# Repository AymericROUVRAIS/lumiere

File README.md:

# Lumiere

Software to control custom connected lamp.

## Objectives

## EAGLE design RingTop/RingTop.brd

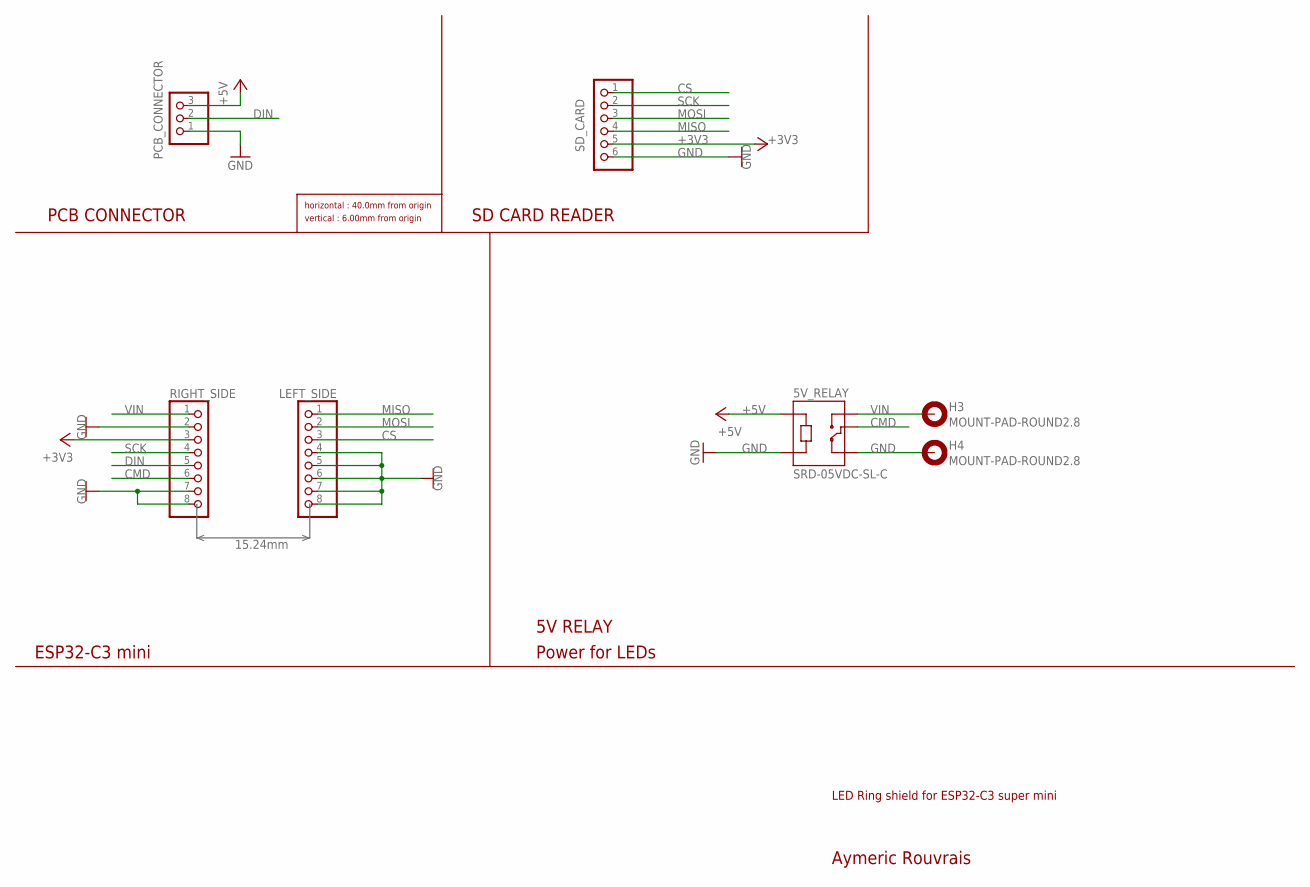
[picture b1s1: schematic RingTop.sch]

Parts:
5V_RELAY: SRD-05VDC-SL-C; RELAY_SRD-05VDC-SL-C
H3, H4: MOUNT-PAD-ROUND2.8; 2,8-PAD
LEFT_SIDE: PINHD-1X8; 1X08
PCB_CONNECTOR: PINHD-1X3; 1X03
RIGHT_SIDE: PINHD-1X8; 1X08
SD_CARD: PINHD-1X6/90; 1X06/90

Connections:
+3V3: RIGHT_SIDE.3, SD_CARD.5
+5V: 5V_RELAY.A1, PCB_CONNECTOR.3
CMD: 5V_RELAY.COM, RIGHT_SIDE.6
CS: LEFT_SIDE.3, SD_CARD.1
DIN: PCB_CONNECTOR.2, RIGHT_SIDE.5
GND: 5V_RELAY.A2, 5V_RELAY.NC, H4.B2,8, LEFT_SIDE.4, LEFT_SIDE.5, LEFT_SIDE.6, LEFT_SIDE.7, LEFT_SIDE.8, PCB_CONNECTOR.1, RIGHT_SIDE.2, RIGHT_SIDE.7, RIGHT_SIDE.8, SD_CARD.6
MISO: LEFT_SIDE.1, SD_CARD.4
MOSI: LEFT_SIDE.2, SD_CARD.3
SCK: RIGHT_SIDE.4, SD_CARD.2
VIN: 5V_RELAY.NO, H3.B2,8, RIGHT_SIDE.1

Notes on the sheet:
LED Ring shield for ESP32-C3 super mini
Aymeric Rouvrais
15.24mm
ESP32-C3 mini
PCB CONNECTOR
SD CARD READER
5V RELAY
Power for LEDs
horizontal : 40.0mm from origin
vertical : 6.00mm from origin

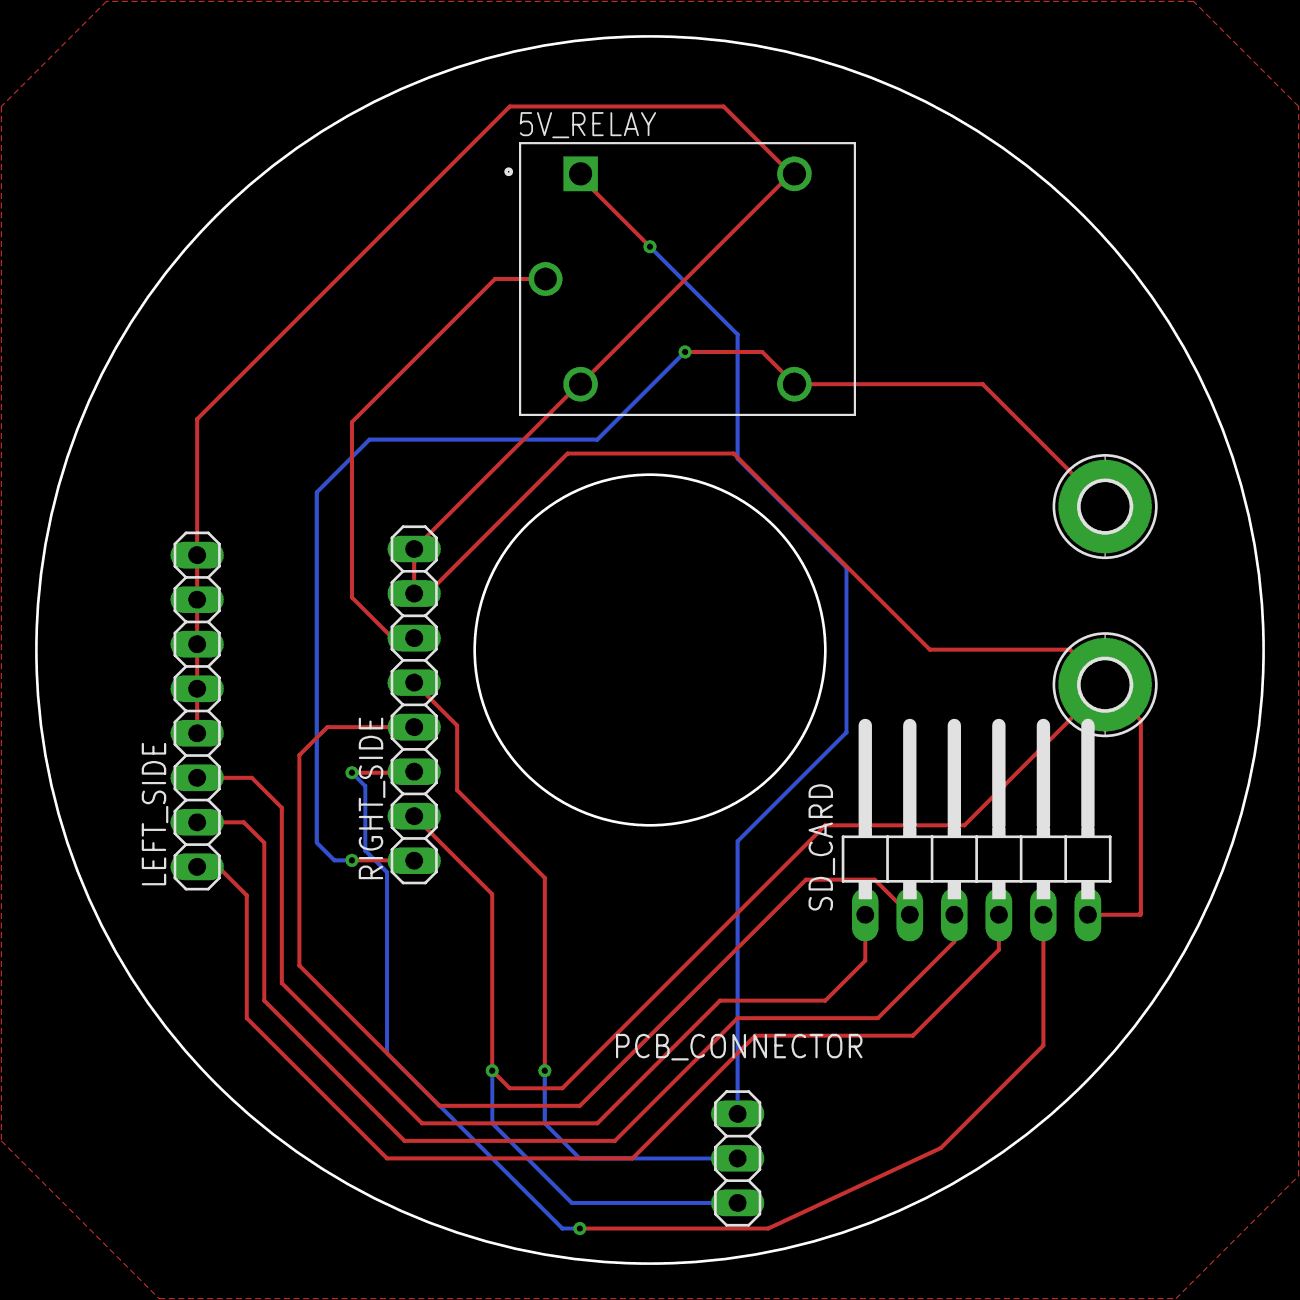
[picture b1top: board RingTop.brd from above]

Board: 2 copper layers, 70.0 x 70.0 mm, 7 parts (0 on the bottom side), 10 nets.

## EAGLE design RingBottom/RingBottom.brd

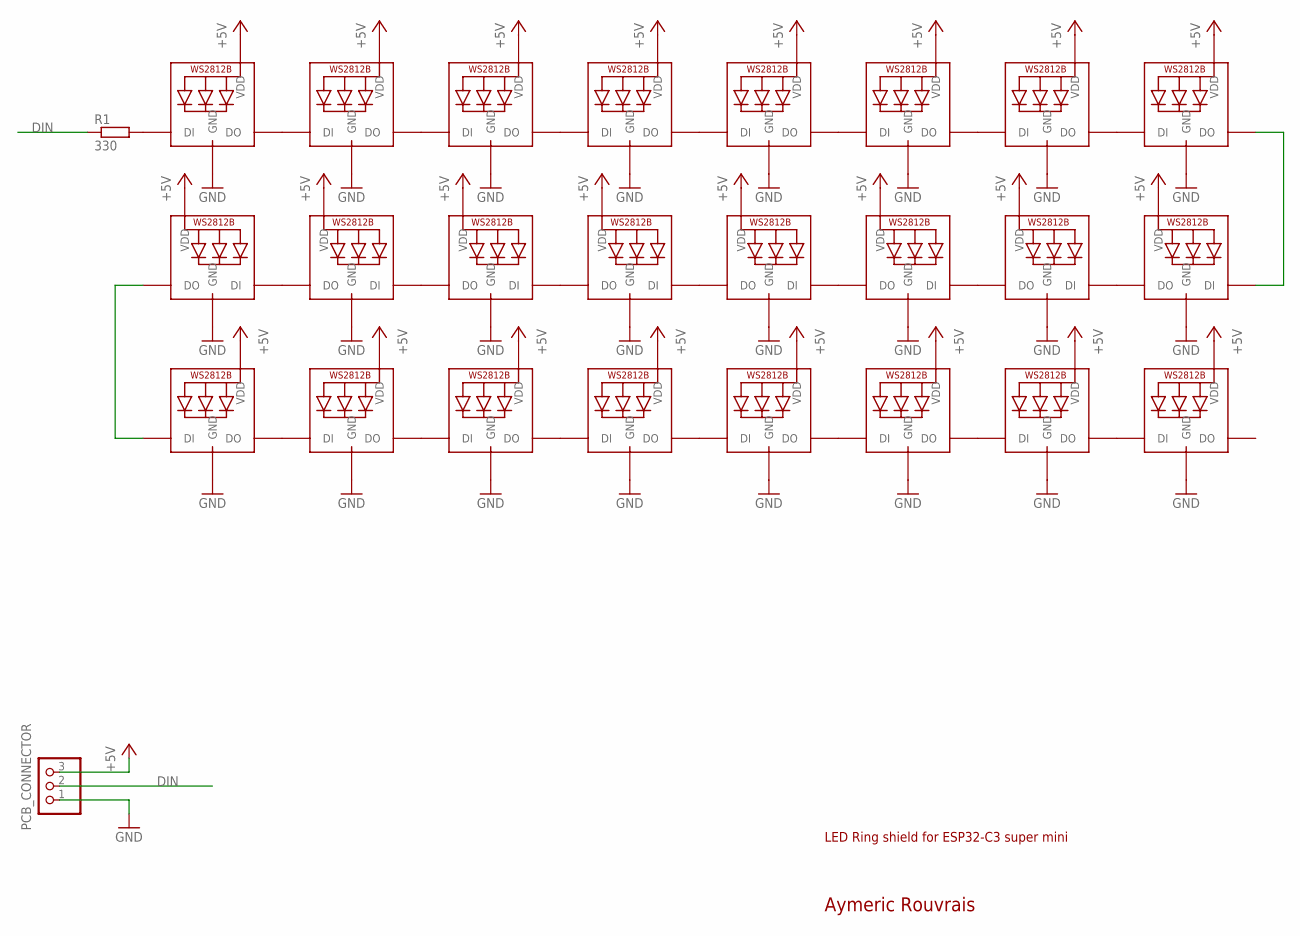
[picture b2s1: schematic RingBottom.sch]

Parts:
LED1, LED2, LED3, LED4, LED5, LED6, LED7, LED8, LED9, LED10, LED11, LED12, LED13, LED14, LED15, LED16, LED17, LED18, LED19, LED20, LED21, LED22, LED23, LED24: WS2812B5050; WS2812B
PCB_CONNECTOR: PINHD-1X3; 1X03
R1: 330; 0204/7

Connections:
+5V: LED1.1-VDD (VDD), LED2.1-VDD (VDD), LED3.1-VDD (VDD), LED4.1-VDD (VDD), LED5.1-VDD (VDD), LED6.1-VDD (VDD), LED7.1-VDD (VDD), LED8.1-VDD (VDD), LED9.1-VDD (VDD), LED10.1-VDD (VDD), LED11.1-VDD (VDD), LED12.1-VDD (VDD), LED13.1-VDD (VDD), LED14.1-VDD (VDD), LED15.1-VDD (VDD), LED16.1-VDD (VDD), LED17.1-VDD (VDD), LED18.1-VDD (VDD), LED19.1-VDD (VDD), LED20.1-VDD (VDD), LED21.1-VDD (VDD), LED22.1-VDD (VDD), LED23.1-VDD (VDD), LED24.1-VDD (VDD), PCB_CONNECTOR.3
DIN: PCB_CONNECTOR.2, R1.1
GND: LED1.3-GND (GND), LED2.3-GND (GND), LED3.3-GND (GND), LED4.3-GND (GND), LED5.3-GND (GND), LED6.3-GND (GND), LED7.3-GND (GND), LED8.3-GND (GND), LED9.3-GND (GND), LED10.3-GND (GND), LED11.3-GND (GND), LED12.3-GND (GND), LED13.3-GND (GND), LED14.3-GND (GND), LED15.3-GND (GND), LED16.3-GND (GND), LED17.3-GND (GND), LED18.3-GND (GND), LED19.3-GND (GND), LED20.3-GND (GND), LED21.3-GND (GND), LED22.3-GND (GND), LED23.3-GND (GND), LED24.3-GND (GND), PCB_CONNECTOR.1
unnamed: LED1.2-DOUT (DO), LED2.4-DIN (DI)
unnamed: LED2.2-DOUT (DO), LED3.4-DIN (DI)
unnamed: LED3.2-DOUT (DO), LED4.4-DIN (DI)
unnamed: LED1.4-DIN (DI), R1.2
unnamed: LED6.2-DOUT (DO), LED7.4-DIN (DI)
unnamed: LED7.2-DOUT (DO), LED8.4-DIN (DI)
unnamed: LED16.2-DOUT (DO), LED17.4-DIN (DI)
unnamed: LED15.2-DOUT (DO), LED16.4-DIN (DI)
unnamed: LED12.2-DOUT (DO), LED13.4-DIN (DI)
unnamed: LED4.2-DOUT (DO), LED5.4-DIN (DI)
unnamed: LED11.2-DOUT (DO), LED12.4-DIN (DI)
unnamed: LED8.2-DOUT (DO), LED9.4-DIN (DI)
unnamed: LED17.2-DOUT (DO), LED18.4-DIN (DI)
unnamed: LED18.2-DOUT (DO), LED19.4-DIN (DI)
unnamed: LED19.2-DOUT (DO), LED20.4-DIN (DI)
unnamed: LED5.2-DOUT (DO), LED6.4-DIN (DI)
unnamed: LED22.2-DOUT (DO), LED23.4-DIN (DI)
unnamed: LED23.2-DOUT (DO), LED24.4-DIN (DI)
unnamed: LED21.2-DOUT (DO), LED22.4-DIN (DI)
unnamed: LED10.2-DOUT (DO), LED11.4-DIN (DI)
unnamed: LED14.2-DOUT (DO), LED15.4-DIN (DI)
unnamed: LED13.2-DOUT (DO), LED14.4-DIN (DI)
unnamed: LED9.2-DOUT (DO), LED10.4-DIN (DI)
unnamed: LED20.2-DOUT (DO), LED21.4-DIN (DI)

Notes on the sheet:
LED Ring shield for ESP32-C3 super mini
Aymeric Rouvrais

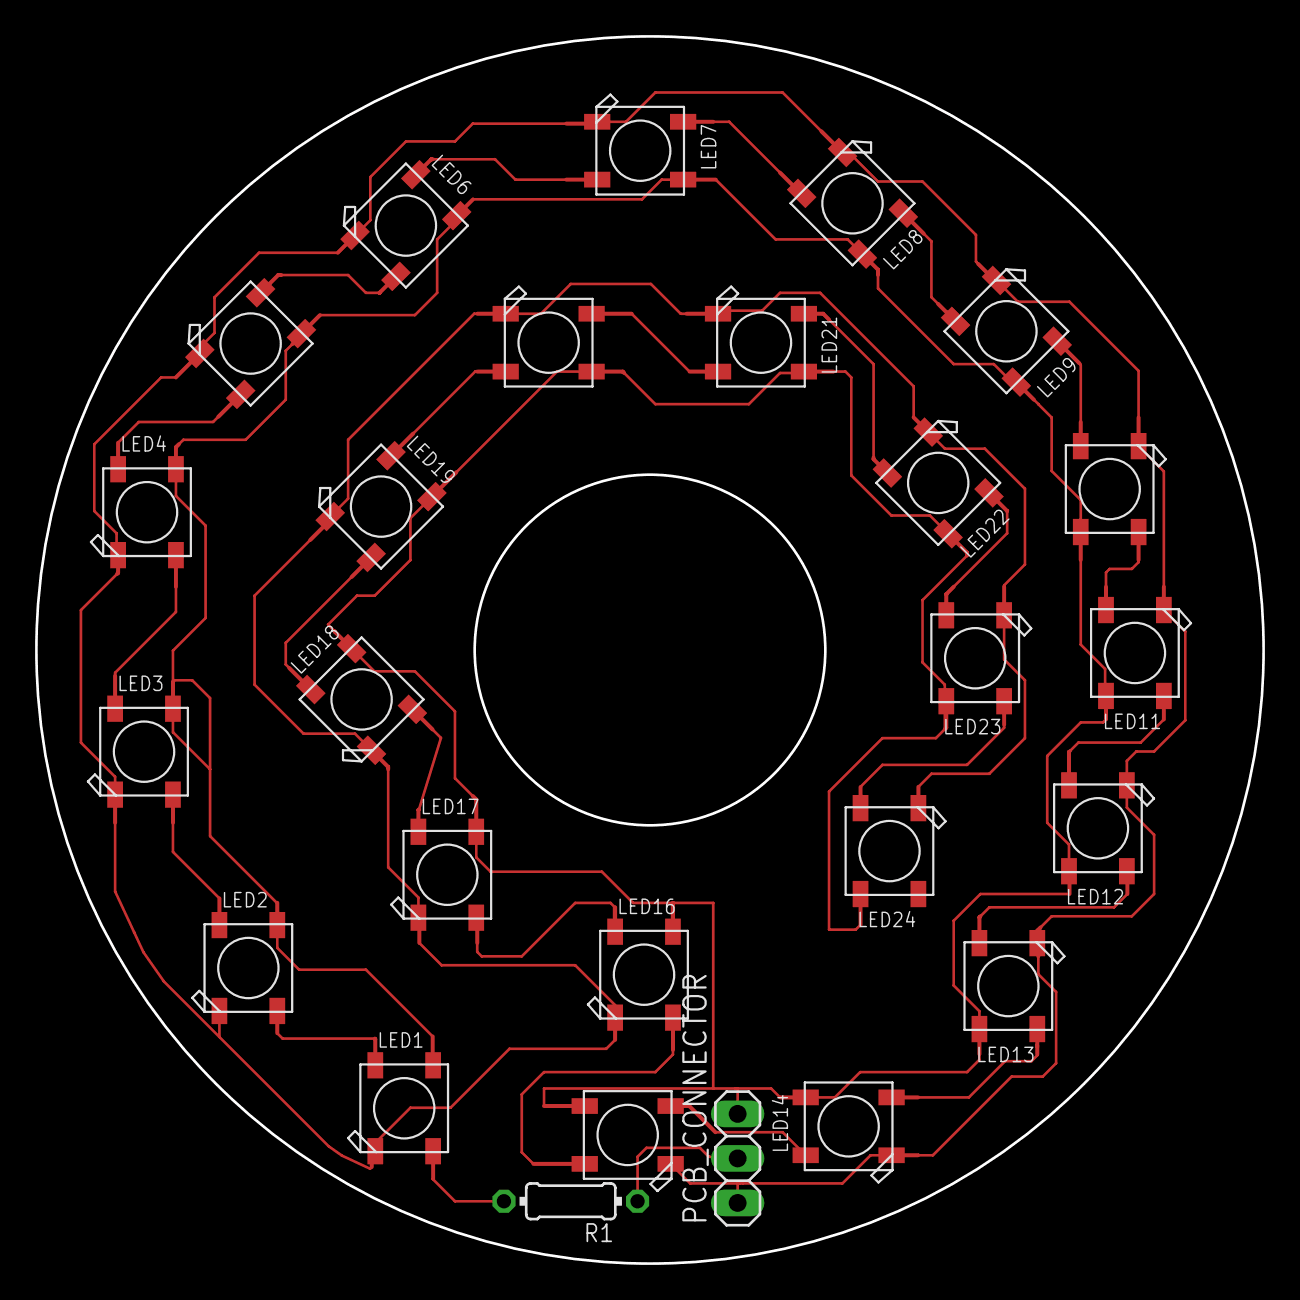
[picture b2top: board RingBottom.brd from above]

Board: 2 copper layers, 70.0 x 70.0 mm, 26 parts (0 on the bottom side), 27 nets.

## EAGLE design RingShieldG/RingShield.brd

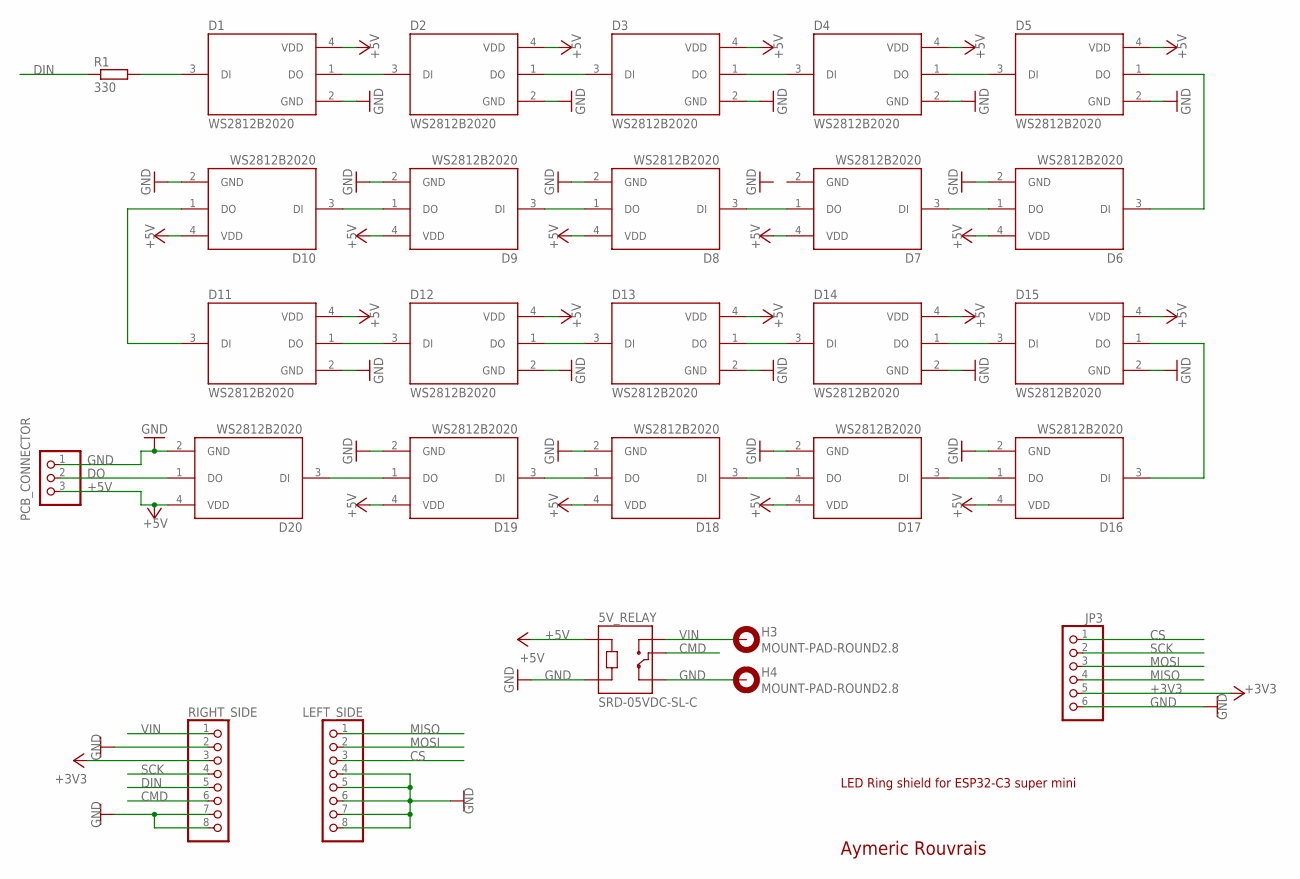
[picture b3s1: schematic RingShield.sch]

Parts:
5V_RELAY: SRD-05VDC-SL-C; RELAY_SRD-05VDC-SL-C
D1, D2, D3, D4, D5, D6, D7, D8, D9, D10, D11, D12, D13, D14, D15, D16, D17, D18, D19, D20: WS2812B2020; LED_WS2812B2020
H3, H4: MOUNT-PAD-ROUND2.8; 2,8-PAD
JP3: PINHD-1X6/90; 1X06/90
LEFT_SIDE: PINHD-1X8; 1X08
PCB_CONNECTOR: PINHD-1X3/90; 1X03/90
R1: 330; 0204/7
RIGHT_SIDE: PINHD-1X8; 1X08

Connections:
+3V3: JP3.5, RIGHT_SIDE.3
+5V: 5V_RELAY.A1, D1.4 (VDD), D2.4 (VDD), D3.4 (VDD), D4.4 (VDD), D5.4 (VDD), D6.4 (VDD), D7.4 (VDD), D8.4 (VDD), D9.4 (VDD), D10.4 (VDD), D11.4 (VDD), D12.4 (VDD), D13.4 (VDD), D14.4 (VDD), D15.4 (VDD), D16.4 (VDD), D17.4 (VDD), D18.4 (VDD), D19.4 (VDD), D20.4 (VDD), PCB_CONNECTOR.3
CMD: 5V_RELAY.COM, RIGHT_SIDE.6
CS: JP3.1, LEFT_SIDE.3
DIN: R1.1, RIGHT_SIDE.5
DO: D20.1 (DO), PCB_CONNECTOR.2
GND: 5V_RELAY.A2, 5V_RELAY.NC, D1.2 (GND), D2.2 (GND), D3.2 (GND), D4.2 (GND), D5.2 (GND), D6.2 (GND), D7.2 (GND), D8.2 (GND), D9.2 (GND), D10.2 (GND), D11.2 (GND), D12.2 (GND), D13.2 (GND), D14.2 (GND), D15.2 (GND), D16.2 (GND), D17.2 (GND), D18.2 (GND), D19.2 (GND), D20.2 (GND), H4.B2,8, JP3.6, LEFT_SIDE.4, LEFT_SIDE.5, LEFT_SIDE.6, LEFT_SIDE.7, LEFT_SIDE.8, PCB_CONNECTOR.1, RIGHT_SIDE.2, RIGHT_SIDE.7, RIGHT_SIDE.8
MISO: JP3.4, LEFT_SIDE.1
MOSI: JP3.3, LEFT_SIDE.2
unnamed: D1.3 (DI), R1.2
unnamed: D1.1 (DO), D2.3 (DI)
unnamed: D2.1 (DO), D3.3 (DI)
unnamed: D3.1 (DO), D4.3 (DI)
unnamed: D4.1 (DO), D5.3 (DI)
unnamed: D5.1 (DO), D6.3 (DI)
unnamed: D18.1 (DO), D19.3 (DI)
unnamed: D9.1 (DO), D10.3 (DI)
unnamed: D8.1 (DO), D9.3 (DI)
unnamed: D7.1 (DO), D8.3 (DI)
unnamed: D6.1 (DO), D7.3 (DI)
unnamed: D14.1 (DO), D15.3 (DI)
unnamed: D13.1 (DO), D14.3 (DI)
unnamed: D12.1 (DO), D13.3 (DI)
unnamed: D11.1 (DO), D12.3 (DI)
unnamed: D10.1 (DO), D11.3 (DI)
unnamed: D17.1 (DO), D18.3 (DI)
unnamed: D16.1 (DO), D17.3 (DI)
unnamed: D15.1 (DO), D16.3 (DI)
unnamed: D19.1 (DO), D20.3 (DI)
SCK: JP3.2, RIGHT_SIDE.4
VIN: 5V_RELAY.NO, H3.B2,8, RIGHT_SIDE.1

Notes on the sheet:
LED Ring shield for ESP32-C3 super mini
Aymeric Rouvrais

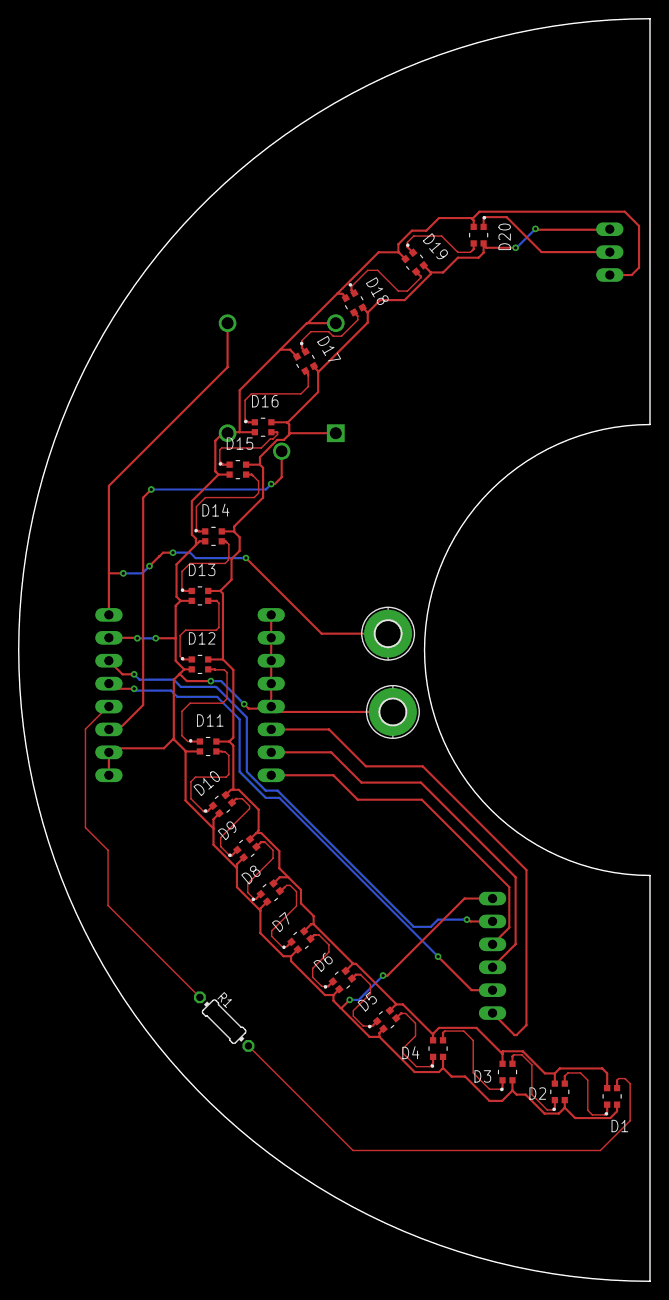
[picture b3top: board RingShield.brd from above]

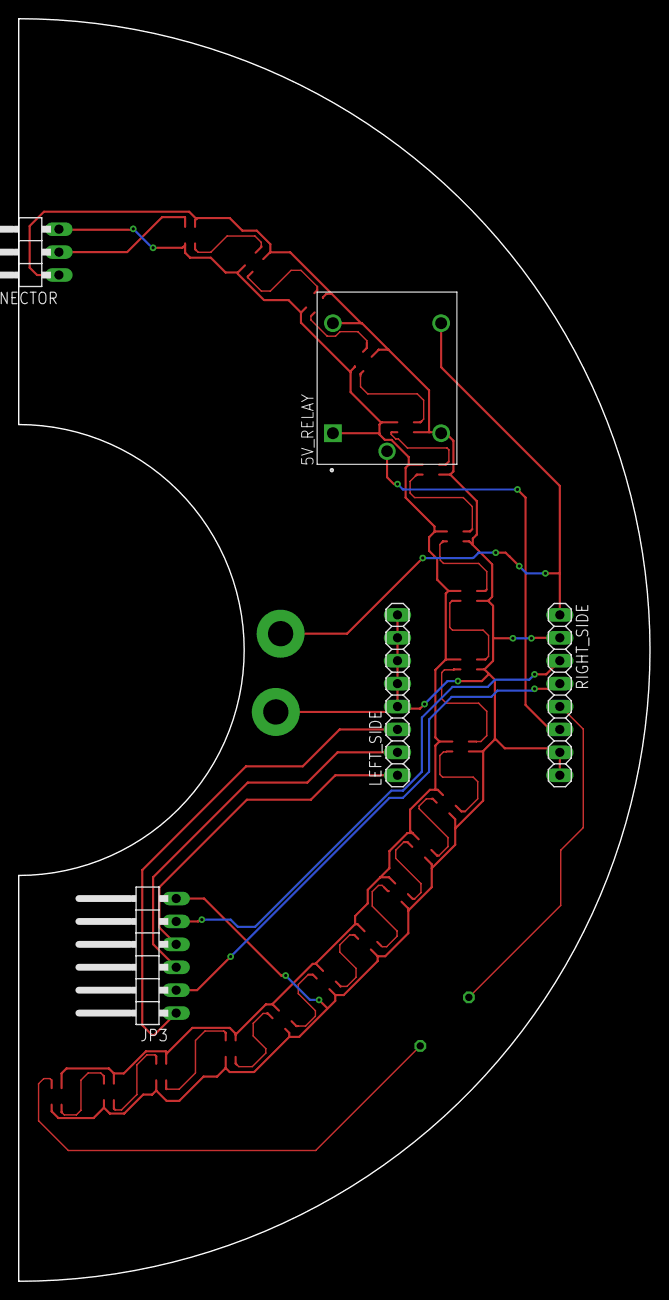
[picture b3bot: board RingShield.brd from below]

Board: 2 copper layers, 70.0 x 140.0 mm, 28 parts (5 on the bottom side), 31 nets.

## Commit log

2025-07-08 Adding all the files
2025-10-16 Working on FAB
    Finished settings page, and some cards
2025-10-16 Creating expanding tile
    Changing the MainCard to be used as expanding tile
2025-10-18 Adding custom slider
    Filling slider, an ios like slider
2025-10-18 Creating custom dialog box for alarms
2025-10-18 Correct implementation of MainCard
2025-10-18 Better library management
2025-10-18 Better functions implementation
    Augmenting code readability
2025-10-18 Better functions use
2025-10-18 Debugging
    InactiveTrackColor isn't recognized in dark and light mode, whereas activeTrackColor is
2025-10-19 Update README with project objectives and tasks
    Added objectives and to-do list for the project.
2025-10-19 Added packages used
2025-10-19 Fix project name capitalization and add branch info
    Corrected capitalization of the project name and added a section for branch information.
2025-10-19 Updating wrong link
2025-10-19 Updating package list
    Updated the README to clarify the section on packages used in the app.
2025-10-19 Added custom widget for light control
    Removed unnecessary files, due to the integration of the widget. And correct packages for the widget
2025-10-19 Updating app functions
2025-10-19 Modifying themes
2025-10-19 Generalizing card theme
2025-10-19 Updating readme
    Updated README to clarify objectives and remove redundant sections.
2025-10-19 Add image placeholder to README
    Added an image placeholder to the README.
2025-10-19 Adding image
2025-10-19 Rename Screenshot 2025-10-19 125306.png to main_page.png
2025-10-19 Update README with image and project description
2025-10-19 Correcting image size
    Updated image syntax in README to HTML format.
2025-10-19 Correct image tag syntax in README.md
    Fix HTML syntax for image tag in README.
2025-10-19 Corrected image
2025-10-19 Add example image to README.md
    Added an example image of the main page of the app.
2025-10-19 Fix formatting issues in README.md
2025-10-19 Resizing image
2025-10-19 Adding dark theme example
2025-10-19 Adding dark mode to README
2025-10-19 Minor corrections
2025-10-19 Added locked ExpansionTile
2025-10-19 Add toggle switch package to README
2025-10-19 Adding theme for ToggleSwitch
2025-10-19 Updating the dialog box
2025-10-19 Small adjustments
    Correcting the fab, and the order of the packages
2025-10-20 Cleaned unused file
2025-10-20 Custom theme for the card inside a dialog
2025-10-20 Updating alarm dialog
2025-10-20 Little cleanup
2025-10-20 Added lamp image to the dialog
2025-10-20 Added time selection
2025-10-20 Finished alarm dialog popup
    The alarm part now adds an alarm on the homepage.
    There is still the other part of the pop up dialog to do, and to make a nice card inside the ExpansionTile
2025-10-20 Changing the border of the card inside dialog
2025-10-24 Cleaning up
2025-10-24 Updating cards
2026-01-12 Updating readme
2026-02-03 Adding v1.2
2026-02-03 Adding v1.4
2026-02-03 Modifying the layout
    Adding 2 folders for 2 pcb, as layout is limiter
2026-02-03 Chagnging right side
2026-02-03 Did part D
2026-02-15 Removing compilation files
2026-02-15 Updating for better integration
    V2 of file
2026-02-15 Updating right board
2026-02-15 Removing compilation files from EAGLE
2026-02-15 Updating left to v2
2026-02-15 Updating leds to correct orientation
    Leads to less via's used
2026-04-11 V2.0
    Now there is a top and bottom PCB. They have the correct dimensions.
    The bottom one has the LEDs and the top one has all the rest.
    There is still a possibility to integrate a sd card
